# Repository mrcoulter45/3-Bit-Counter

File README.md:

# 3-Bit Counter
This is a 3-bit counter project I made because I was interested in trying my hand at a custon PCB. The PCB was made by JLCPCB, and turned out really good. The counter operates via NAND and D flip-flop ICs, the Arduino Nano is used simply for a clk signal to the chips. 
The 3-bit counter consists of:
- x4 MH7420 (SN7420N / NTE7420) DUAL 4-INPUT NAND 7420 ICs
- x2 CD4013B CMOS Dual D-Type Flip-Flop ICs
- x1 Arduino Nano
- x3 5mm blue LEDs
- x3 220Ω resistors
- x2 10nf monolithic capacitors
- x2 100nf monolithic capacitors
- PCB

__________
  
## 3-Bit Counter v1
Here is the first version of the counter that I made with a PCB milling machine. It was much more difficult to make, in that I had to solder every pin on both sides of the PCB, as well as solder wires to both sides of the PCB for every via. It doesn't work so well because it doesn't have capacitors and the copper became very corroded over time.  

__________  

---

## 🎥 Video of 3-Bit Counter Logic Circuit

<p align="center">
  <a href="https://youtu.be/tnVruFOkVYI" target="_blank" style="text-decoration:none;">
    <span style="position: relative; display: inline-block;">
      
  </a>
</p>

---

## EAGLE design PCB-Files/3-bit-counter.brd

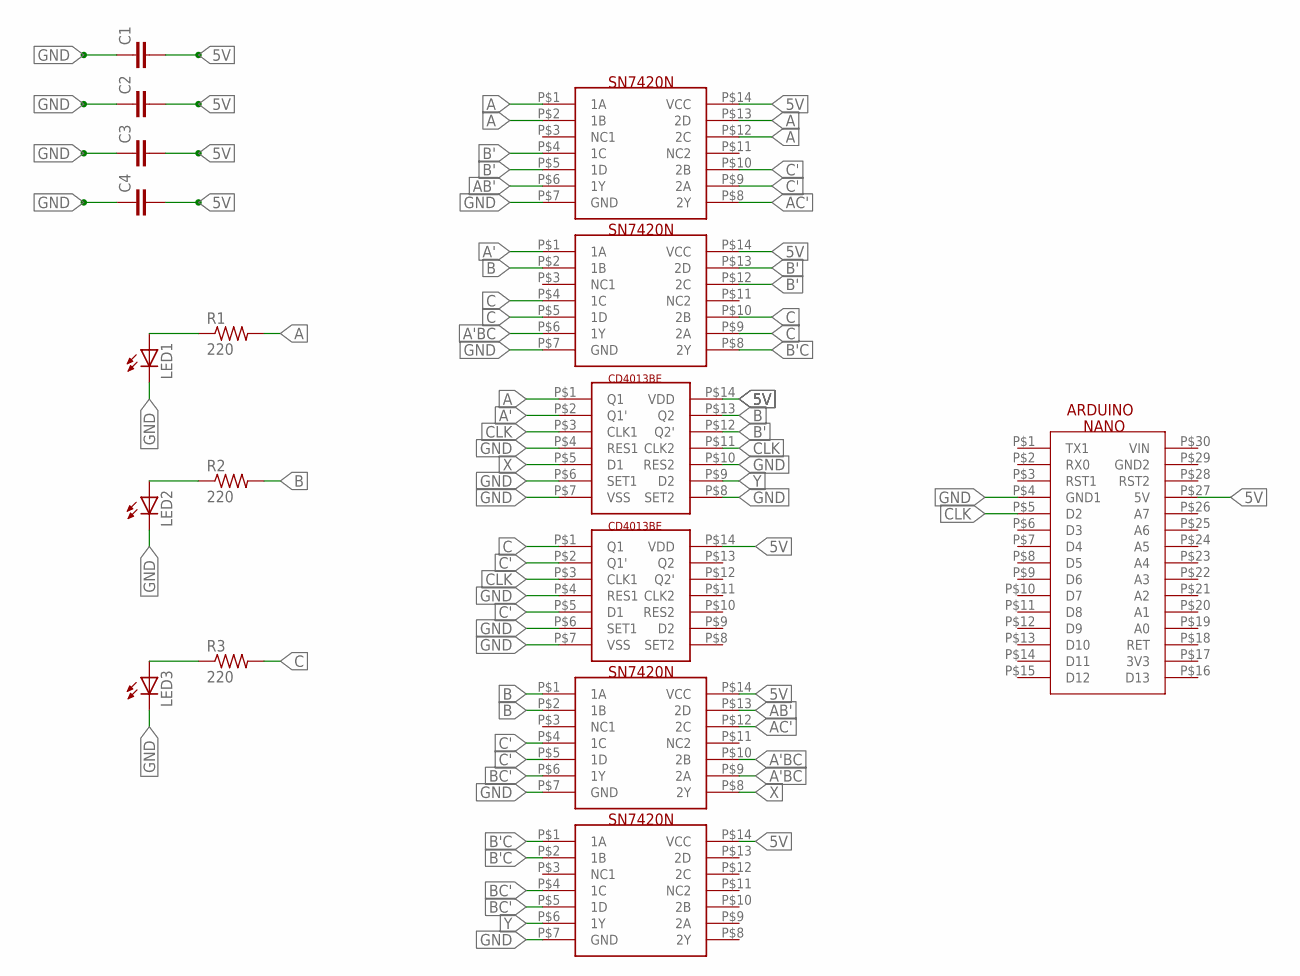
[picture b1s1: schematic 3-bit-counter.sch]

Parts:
C1, C2, C3, C4: C2,5-3; C2.5-3
DFF1, DFF2: MC_DFFDIP14; DIP14
LED1, LED2, LED3: LED5MM
NAND1, NAND2, NAND3, NAND4: MC_NANDDIP14; DIP14
R1, R2, R3: 220; 0204/7
U$7: MC_NANO

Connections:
5V: C1.2, C2.2, C3.2, C4.2, DFF1.P$14 (VDD), DFF2.P$14 (VDD), NAND1.P$14 (VCC), NAND2.P$14 (VCC), NAND3.P$14 (VCC), NAND4.P$14 (VCC), U$7.P$27 (5V)
A: DFF1.P$1 (Q1), NAND1.P$1 (1A), NAND1.P$2 (1B), NAND1.P$12 (2C), NAND1.P$13 (2D), R1.2
A': DFF1.P$2 (Q1'), NAND2.P$1 (1A)
A'BC: NAND2.P$6 (1Y), NAND3.P$9 (2A), NAND3.P$10 (2B)
AB': NAND1.P$6 (1Y), NAND3.P$13 (2D)
AC': NAND1.P$8 (2Y), NAND3.P$12 (2C)
B: DFF1.P$13 (Q2), NAND2.P$2 (1B), NAND3.P$1 (1A), NAND3.P$2 (1B), R2.2
B': DFF1.P$12 (Q2'), NAND1.P$4 (1C), NAND1.P$5 (1D), NAND2.P$12 (2C), NAND2.P$13 (2D)
B'C: NAND2.P$8 (2Y), NAND4.P$1 (1A), NAND4.P$2 (1B)
BC': NAND3.P$6 (1Y), NAND4.P$4 (1C), NAND4.P$5 (1D)
C: DFF2.P$1 (Q1), NAND2.P$4 (1C), NAND2.P$5 (1D), NAND2.P$9 (2A), NAND2.P$10 (2B), R3.2
C': DFF2.P$2 (Q1'), DFF2.P$5 (D1), NAND1.P$9 (2A), NAND1.P$10 (2B), NAND3.P$4 (1C), NAND3.P$5 (1D)
CLK: DFF1.P$3 (CLK1), DFF1.P$11 (CLK2), DFF2.P$3 (CLK1), U$7.P$5 (D2)
GND: C1.1, C2.1, C3.1, C4.1, DFF1.P$4 (RES1), DFF1.P$6 (SET1), DFF1.P$7 (VSS), DFF1.P$8 (SET2), DFF1.P$10 (RES2), DFF2.P$4 (RES1), DFF2.P$6 (SET1), DFF2.P$7 (VSS), LED1.K (C), LED2.K (C), LED3.K (C), NAND1.P$7 (GND), NAND2.P$7 (GND), NAND3.P$7 (GND), NAND4.P$7 (GND), U$7.P$4 (GND1)
unnamed: LED3.A, R3.1
unnamed: LED2.A, R2.1
unnamed: LED1.A, R1.1
X: DFF1.P$5 (D1), NAND3.P$8 (2Y)
Y: DFF1.P$9 (D2), NAND4.P$6 (1Y)

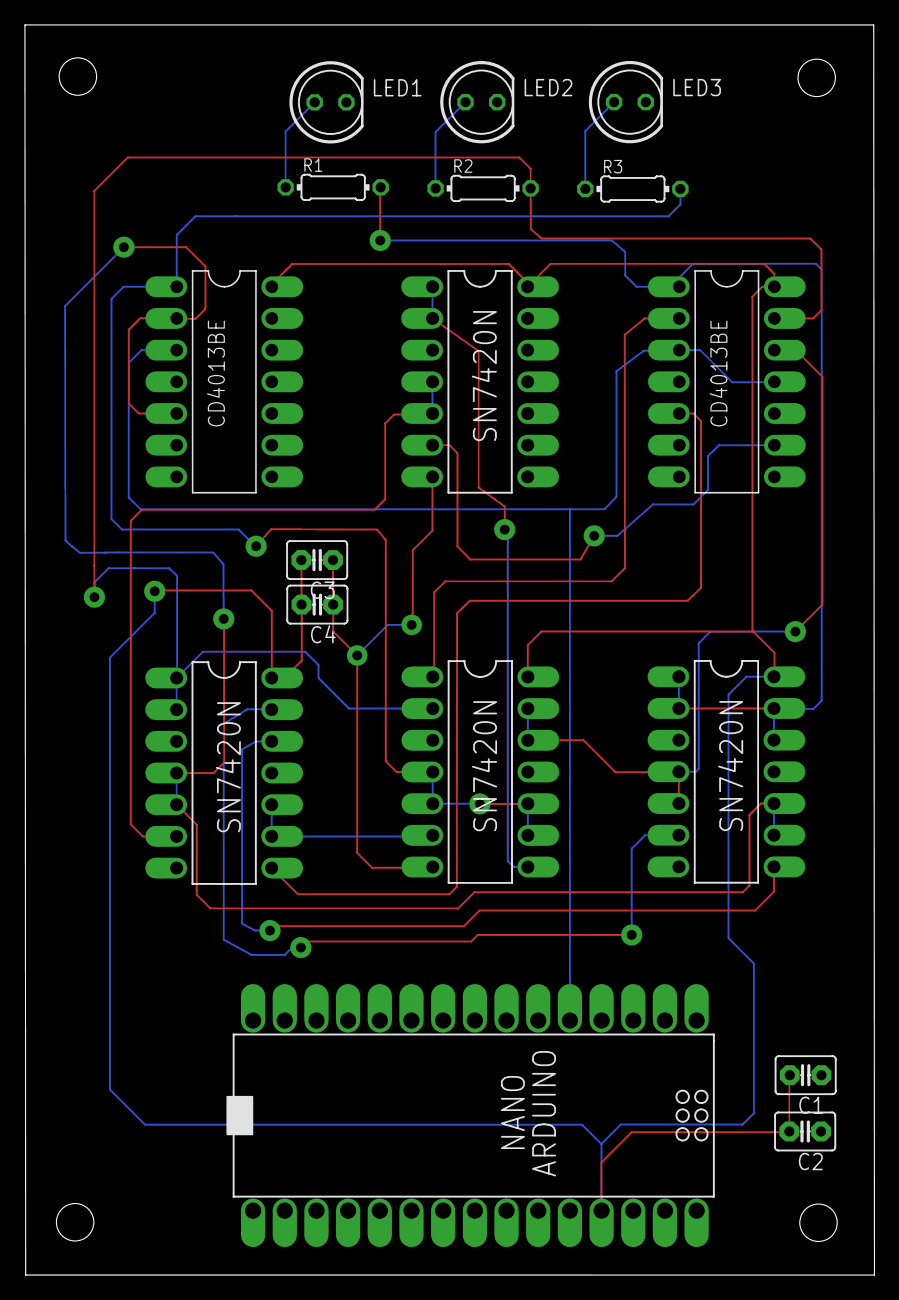
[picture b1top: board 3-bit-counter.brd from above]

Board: 2 copper layers, 68.1 x 100.2 mm, 17 parts (0 on the bottom side), 19 nets.

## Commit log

2019-04-20 Add NAND and D-FF chip testers
2019-04-20 Edit README and add pic/gif
2019-04-20 Edit README
2019-04-20 Edit pics
2019-04-20 Edit README and pics
2019-04-20 Add pics and edit README
2025-11-03 Add video section for 3-Bit Counter
    Added a video link and thumbnail for the 3-Bit Counter logic circuit.
